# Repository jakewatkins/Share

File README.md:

# Share
repo for my trashcode stuff to share with others

- googleCalendar
agent to access Google Calendar
- owaAgent
access exchange server
- outlookAgent 
get email from outlook.com

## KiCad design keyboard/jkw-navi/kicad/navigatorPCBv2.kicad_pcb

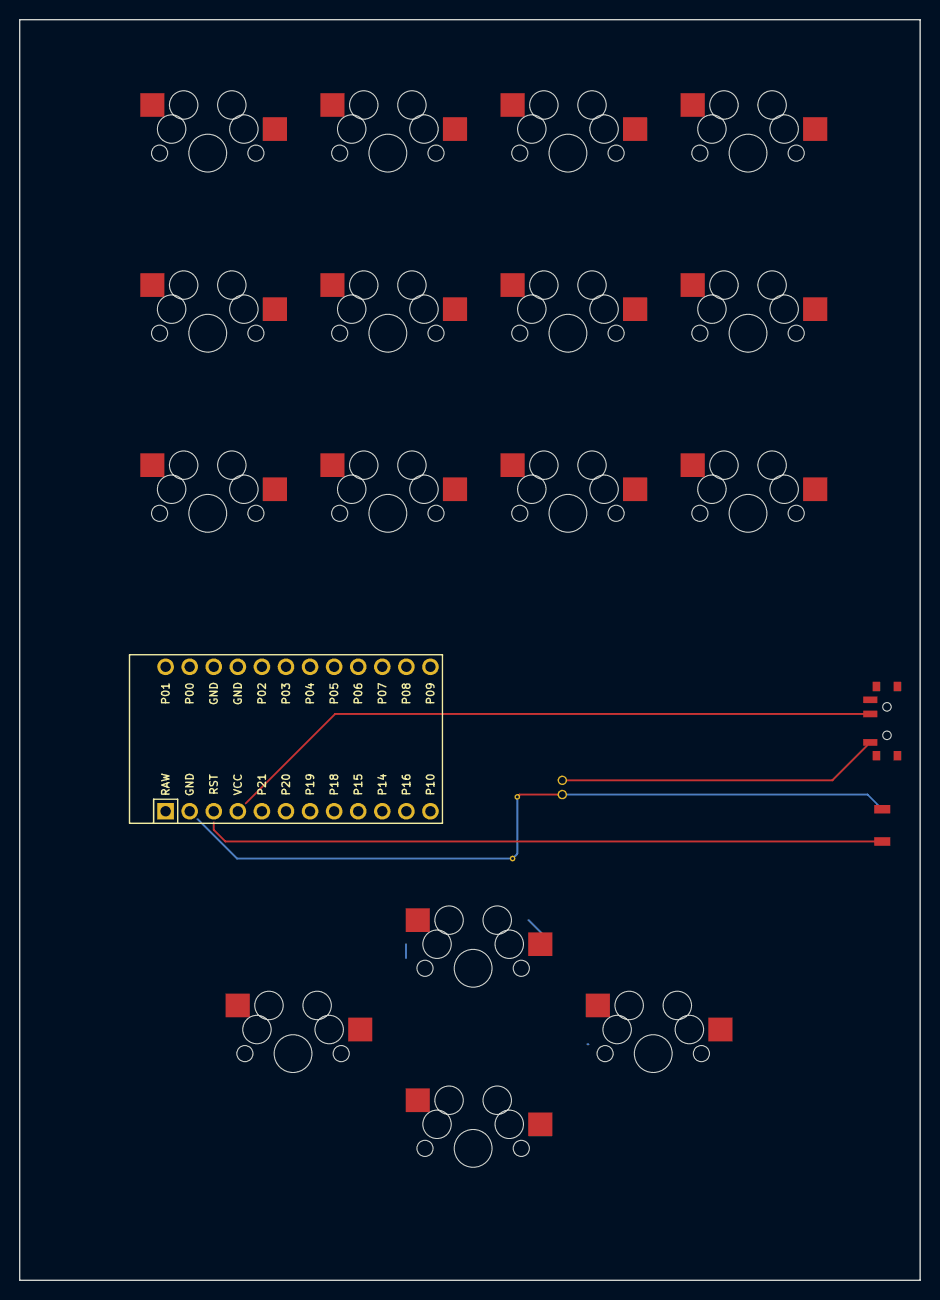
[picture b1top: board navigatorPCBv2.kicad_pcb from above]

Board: 2 copper layers, 95.0 x 133.0 mm, 17 parts (0 on the bottom side), 16 nets.

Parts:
MCU1: ProMicro
S1, S2, S3, S4, S5, S6, S7, S8, S9, S10, S11, S12, S13, S14, S15, S16: MX

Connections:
GND: MCU1.2, MCU1.15, MCU1.16, S1.1, S2.1, S3.1, S4.1, S5.1, S6.1, S7.1, S8.1, S9.1, S10.1, S11.1, S12.1, S13.1, S14.1, S15.1, S16.1
macropad_index_bottom: MCU1.18, S10.2
macropad_index_middle: MCU1.11, S11.2
macropad_index_top: MCU1.6, S12.2
macropad_middle_bottom: MCU1.17, S7.2
macropad_middle_middle: MCU1.10, S8.2
macropad_middle_top: MCU1.7, S9.2
macropad_pinky_bottom: MCU1.12, S1.2
macropad_pinky_middle: MCU1.5, S2.2
macropad_pinky_top: MCU1.22, S3.2
macropad_ring_bottom: MCU1.13, S4.2
macropad_ring_middle: MCU1.9, S5.2
macropad_ring_top: MCU1.8, S6.2
navigator_right_down: MCU1.23, S16.2
navigator_updown_down: MCU1.21, S14.2
navigator_updown_up: MCU1.20, S15.2

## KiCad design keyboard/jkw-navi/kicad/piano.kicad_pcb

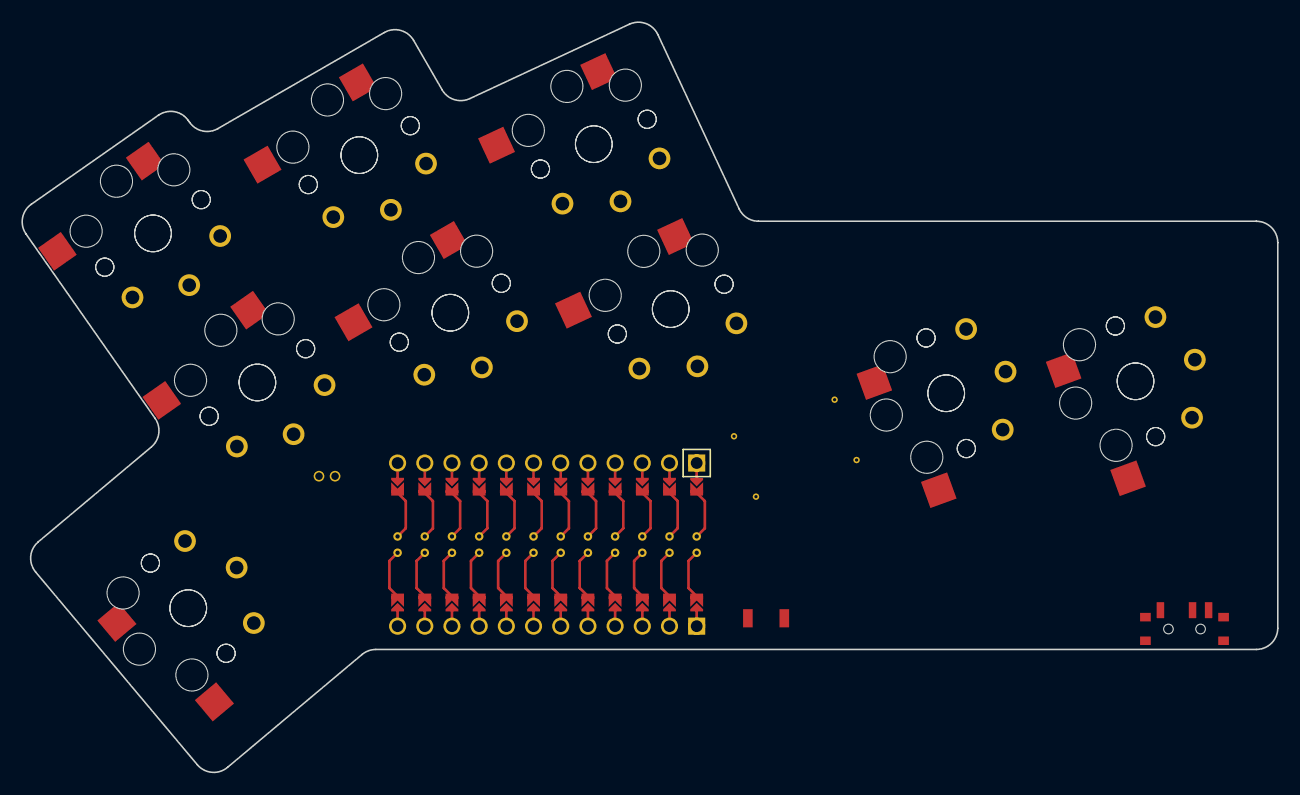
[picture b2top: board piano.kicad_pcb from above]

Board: 2 copper layers, 117.3 x 70.1 mm, 19 parts (0 on the bottom side), 10 nets, no tracks yet.

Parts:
MCU1: ProMicro
S1, S2, S3, S4, S5, S6, S7, S8, S9, S10, S11, S12, S13, S14, S15, S16, S17, S18: PG1350

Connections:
GND: MCU1.2, MCU1.21, MCU1.22, S1.2, S2.2, S3.2, S4.2, S5.2, S6.2, S7.2, S8.2, S9.2, S10.2, S11.2, S12.2, S13.2, S14.2, S15.2, S16.2, S17.2, S18.2
P0: MCU1.23, S15.1, S16.1
P1: MCU1.24, S17.1, S18.1
P4: MCU1.18, S11.1, S12.1
P5: MCU1.17, S13.1, S14.1
P8: MCU1.14, S5.1, S6.1
P9: MCU1.13, S3.1, S4.1
P10: MCU1.12, S1.1, S2.1
P14: MCU1.10, S9.1, S10.1
P15: MCU1.9, S7.1, S8.1

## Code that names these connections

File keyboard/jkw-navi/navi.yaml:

presets:
  # These presets provide different layout options
  # Select a preset in the `units` section below
  # Note: The appropriate switch footprint will still need to be set in the `pcb` section
  defaults:
    edgex: 16       # Edge cut distance horizontal
    edgey: 16       # Edge cut distance vertical
    capx: 17        # Key cap size horizontal
    capy: 16        # Key cap size vertical
    kx: 18.5        # Key spacing horizontal
    ky: 17.5        # Key spacing vertical
    pinky_splay: 5  # Degrees of splay between pinky and ring columns
    pinky_adj: -3   # Adjustment to compensate for splay spacing
    ring_splay: 3
    ring_adj: -8
    middle_splay: 0
    middle_adj: 0


points:
  zones:
    macropad:
      columns:
        pinky:
        ring:
        middle:
        index:
      rows:
        bottom:
        middle:
        top:

    navigator:
      anchor:
        ref: macropad_ring_top
        shift: [-10,-5u]
      rows:
        down:
        up:
      columns:
        left:
          rows:
            up.skip: true
        updown:
          key:
            stagger: -10
        right:
          key:
            stagger: 10
          rows:
            up.skip: true
outlines:
  macropac_perimeter:
    - what: rectangle
      bound: true
      size: [15, 15]
      where:
        - /macropad_.*/
  navigator_perimeter:
      - what: rectangle
        bound: true
        size: [15, 15]
        where:
          - /navigator_.*/
  pcb_perimeter:
    - what: rectangle
      bound: false
      size: [5u,7u]
      where:
        ref: macropad_pinky_top
        shift: [.5u, .5u]
      
      

pcbs:
  navigatorPCB:
    outlines:
      board:
        outline: pcb_perimeter
    footprints:
      keys:
        what: mx
        where: true
        params:
          from: GND
          to: "{{name}}"
          reverse: true
          keycaps: true
      mcu:
        what: promicro
        where:
          - ref: macropad_pinky_bottom
            shift: [.5U, -1.25U]
          
        params:
          P7: macropad_pinky_top
          P18: macropad_ring_top
          P19: macropad_middle_top
          P20: macropad_index_top
          P21: macropad_pinky_middle
          P15: macropad_ring_middle
          P14: macropad_middle_middle
          P16: macropad_index_middle
          P10: macropad_pinky_bottom
          P1: macropad_ring_bottom
          P2: macropad_middle_bottom
          P3: macropad_index_bottom
          P4: navigator_left_up
          P5: navigator_updown_up
          P6: navigator_updown_down
          P8: navigator_right_down
      battery:
        what: jumper
        params:
          from: VCC
          to: powerswitch
        where:
          - ref: macropad_pinky_bottom
            shift: [5U, 1.25U]   
      powerswitch:
        what: slider
        params:
          from: battery
          to: VCC   
        where:
          - ref: macropad_pinky_bottom
            shift: [5U, 1.5U]        
      reset:
        what: button
        where:
          ref:
            - macropad_pinky_bottom
          shift: [5u, 3u]
          rotate: 90
        params:
          from: RST
          to: GND         
          

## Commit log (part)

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2025-06-17 adding googleCalendar sample
2025-06-18 updated calendar program
2025-06-18 refactoring
2025-06-19 starting email agent
2025-06-19 setting up owaaegent
2025-06-19 owaAgent works
2025-06-19 updated gitignore
2025-06-29 adding keyboard stuff
2025-06-29 removing submodule
2025-06-29 adding ergogen
2025-07-07 outlook agent first commit
2025-07-07 reorganizing solution
2025-07-07 outlookAgent works
2025-07-07 adding ergogen 1key config
2025-07-09 first commit for gmailAgent
2025-07-12 debugging update
2025-07-12 more debugging update
2025-07-12 creating email service library
2025-08-09 added OutlookService to emailService project
2025-08-09 added gmailService to email service
2025-08-09 missing files for GmailService
2025-08-28 code complete, now debugging
2025-10-05 Add NuGet package configuration to emailServices
    - Added package metadata including PackageId, Version, Authors, Description
    - Configured automatic package generation on build (GeneratePackageOnBuild)
    - Added symbol package generation for debugging support
    - Set up proper package tags and repository information
    - Package is now ready for distribution and use in other projects
2025-10-11 Implement IDisposable pattern and refactor connection management for v1.1.0
    - Update package version from 1.0.0 to 1.1.0 for delete functionality
    - Add IDisposable implementation to all three email services:
    * OwaService: Added proper ExchangeService credentials cleanup
    * GmailService: Added proper Gmail service disposal
    * OutlookService: Added proper GraphServiceClient cleanup
    - Refactor connection management for better reusability:
2025-10-11 Implement delete email functionality for all services (Requirements 6, 7, 8)
    Complete implementation of DeleteEmail methods across all three email services:
    **Requirement 6 - OWA DeleteEmail:**
    - Added public bool DeleteEmail(Email email) method
    - Validates service type (OWA) and non-null/empty email ID
    - Uses EWS DeleteItems API with MoveToDeletedItems mode
    - Proper ServiceResponseException handling and logging
2025-10-12 feat: Implement Requirement 9 - Email Services Folder-Based Retrieval v1.2.0
    ✨ New Features:
    - EmailFolder entity with FolderType enum (Inbox, Sent, Drafts, Spam, Trash, Custom)
    - Optional folder parameter in GetEmailRequest with backward compatibility
    - Factory methods for standard folders across all email services
    - Service-specific folder mapping for OWA, Gmail, and Outlook
    🔧 Service Enhancements:
2025-12-09 update before work
2026-01-09 updates for email agent
2026-01-19 adding docker compose for n8n to use https
2026-01-19 outlook agent update
2026-01-20 removing secret from n8n docker-compose file
2026-02-01 Fix Microsoft Graph authentication for personal accounts
    - Upgrade Microsoft.Graph from v4.x to v5.95.0 in both projects
    - Remove deprecated Microsoft.Graph.Auth package
    - Create custom MSALAuthenticationProvider to integrate MSAL.NET with Graph v5
    - Use /consumers authority endpoint to properly support personal Microsoft accounts (@msn.com, @outlook.com, etc.)
    - Update API calls to use Microsoft Graph v5 fluent syntax
    - Fix authentication flow that was preventing personal account login
2026-02-01 Add comprehensive README and enhance VS Code development experience
    - Add detailed README.md with complete setup instructions, project structure overview, and usage guide
    - Document Microsoft Graph v5 migration and personal account authentication fix
    - Include troubleshooting section and security best practices
    - Enhanced VS Code settings with comprehensive IntelliSense and suggestion features:
    * Enable all suggestion types (methods, properties, events, etc.)
    * Add C# inlay hints for types, parameters, and implicit variables
2026-02-03 updates - classfier is working
2026-02-09 emailProcessor update
2026-02-22 Implement persistent token storage for Gmail authentication
    - Added FileDataStore for persistent OAuth token storage
    - Enables one-time authentication without repeated user interaction
    - Tokens stored in gmail_tokens/ directory for automatic refresh
    - Enhanced logging for authentication debugging
    - Consistent with outlookAgent token management pattern
2026-02-22 Implement persistent token storage for Outlook authentication
    - Added Microsoft.Identity.Client.Extensions.Msal package for MSAL token caching
    - Implemented MsalCacheHelper for persistent token storage in outlook_tokens/ directory
    - Enhanced logging for authentication debugging and token cache operations
    - Added fallback to in-memory cache if persistent storage fails
    - Enables one-time authentication without repeated user interaction
    - Matches Gmail service token management pattern for consistency
2026-02-22 Fix OutlookService persistent token storage implementation
    - Remove async/await from constructor (not allowed in C#)
    - Defer graph client initialization to first use
    - Fix syntax error in InitializeGraphClientAsync method
    - Add proper macOS keychain configuration with WithMacKeyChain
    - Update DeleteEmail method to use async EnsureConnectionAsync properly
    - Ensures proper async/await pattern throughout token cache creation
2026-02-22 Add token storage directories to .gitignore
    - Prevent gmail_tokens/ and outlook_tokens/ directories from being committed
    - Protect sensitive OAuth tokens and refresh tokens from accidental exposure
    - Add wildcard pattern *_tokens/ for future token storage directories
2026-02-22 Update README.md with deployment information
    - Add section about pre-built applications available at ~/apps/
    - Include launch script usage instructions for Digital Valet
    - Reference EMAIL_APPS_README.md for detailed deployment docs
    - Reorganize running instructions to prioritize deployed apps
2026-02-22 Fix formatting in README.md deployment section
2026-02-28 Phase 1 & 2: Implement Azure Key Vault OAuth token management
    - Add comprehensive requirements document for Key Vault integration
    - Implement KeyVaultService class for secure token storage operations
    - Create KeyVaultDataStore for Google OAuth2 integration with Key Vault
    - Refactor Gmail service to use Key Vault instead of local file storage
    - Add automatic migration from local tokens to Key Vault
    - Update dependency injection to support KeyVaultService
2026-03-15 Complete Outlook OAuth Token Migration to Azure Key Vault
    - Migrated OutlookService from file-based to Key Vault token storage
    - Implemented KeyVaultTokenCache for MSAL integration
    - Updated all service constructors and dependencies
    - Added comprehensive testing and validation
    - All accounts (Gmail and Outlook) successfully tested
    - Enhanced security with encrypted Key Vault storage
2026-03-15 feat: Add Docker containerization for EmailServices Web API
    Complete implementation of .NET 9 Web API with Docker support:
    - Email operations service with Gmail/Outlook delete functionality
    - Multi-stage Dockerfile with security hardening
    - Docker Compose for development and production
    - Helper scripts and comprehensive documentation
    - Unit and integration tests with xUnit
2026-05-03 unattended operation has been fixed
2026-05-04 added tests for deleting email. Both pass
2026-05-06 containerized deployment and smoke test
2026-05-27 adding deployment script
